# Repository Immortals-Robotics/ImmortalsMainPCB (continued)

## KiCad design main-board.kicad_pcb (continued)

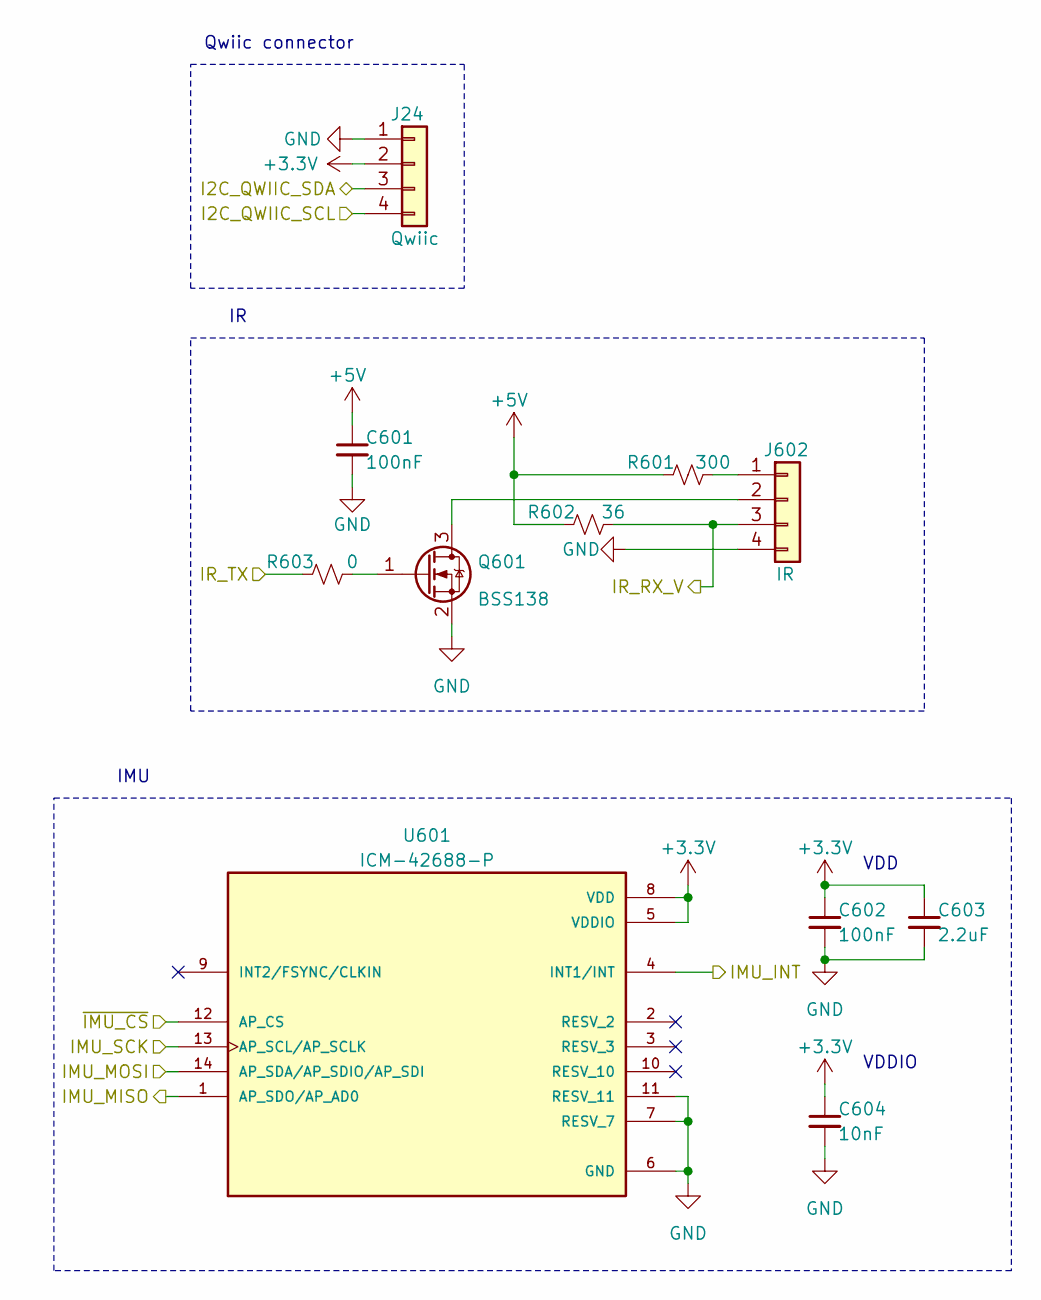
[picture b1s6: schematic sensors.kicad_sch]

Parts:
C601, C602: 100nF; C_0603_1608Metric; MPN RM EMK105 B7104KV-F
C603: 2.2uF; C_0805_2012Metric
C604: 10nF; C_0603_1608Metric
J24: Qwiic; JST_SH_SM04B-SRSS-TB_1x04-1MP_P1.00mm_Horizontal; MPN SM04B-SRSS-TB(LF)(SN)
J602: IR; JST_SH_SM04B-SRSS-TB_1x04-1MP_P1.00mm_Horizontal; MPN SM04B-SRSS-TB(LF)(SN)
Q601: BSS138; SOT-23
R601: 300; R_0603_1608Metric
R602: 36; R_0603_1608Metric
R603: 0; R_0603_1608Metric; MPN RMCF0603ZT0R00
U601: ICM-42688-P; PQFN50P300X250X97-14N

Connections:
+5V: C601.1, R601.1, R602.1; also elsewhere on the board
/CM_SPI1_MISO: U601.1 (AP_SDO/AP_AD0); also elsewhere on the board
/CM_SPI1_MOSI: U601.14 (AP_SDA/AP_SDIO/AP_SDI); also elsewhere on the board
/CM_SPI1_SCK: U601.13 (AP_SCL/AP_SCLK); also elsewhere on the board
/IMU_INT: U601.4 (INT1/INT); also elsewhere on the board
/IR_ADC: J602.3, R602.2; also elsewhere on the board
/IR_PWM: R603.1; also elsewhere on the board
/~CM_SPI1_CS_IMU: U601.12 (AP_CS); also elsewhere on the board
unnamed: J602.1, R601.2
unnamed: J602.2, Q601.3 (D)
unnamed: Q601.1 (G), R603.2

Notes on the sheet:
Qwiic connector
VDD
VDDIO
IMU

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
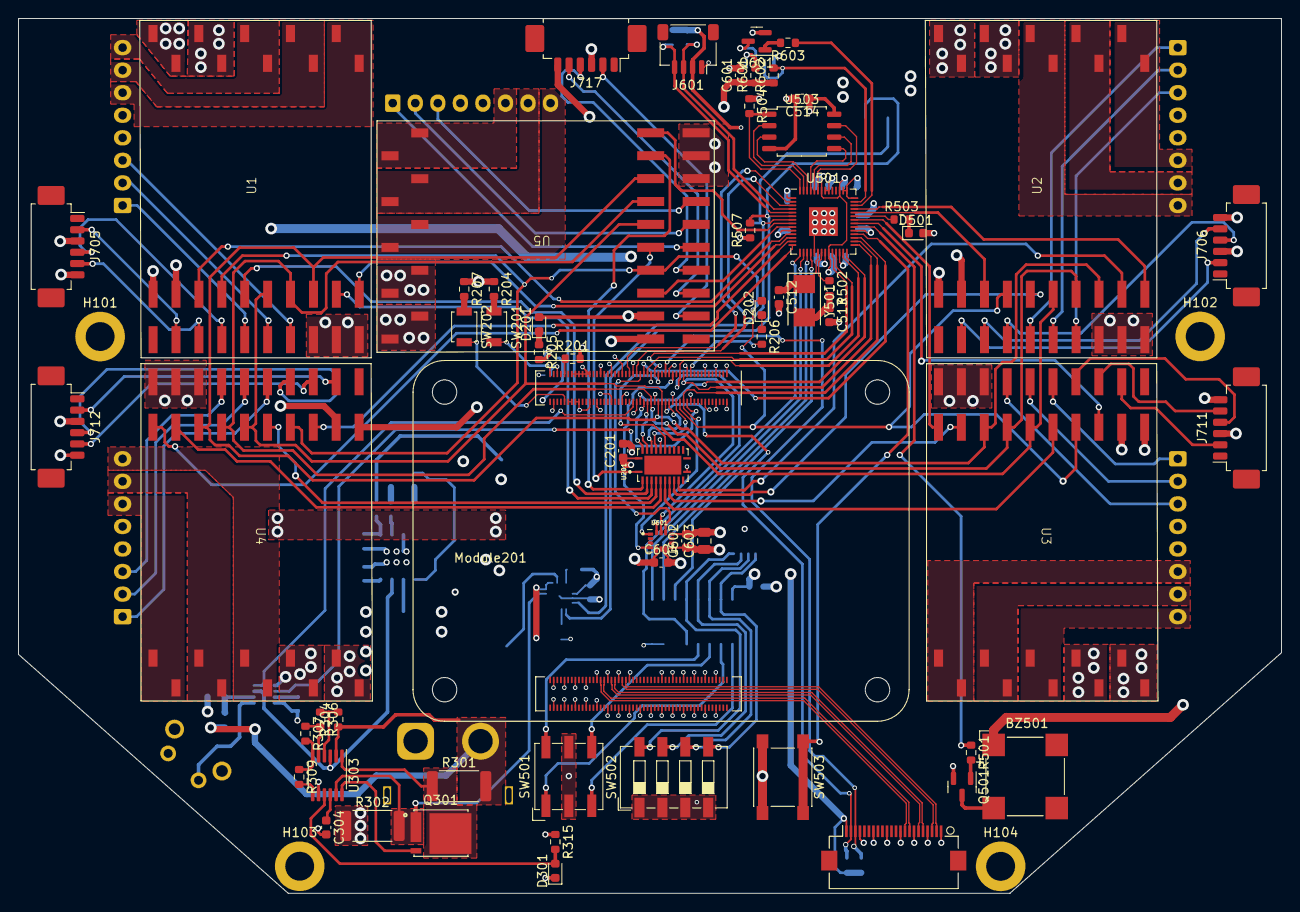
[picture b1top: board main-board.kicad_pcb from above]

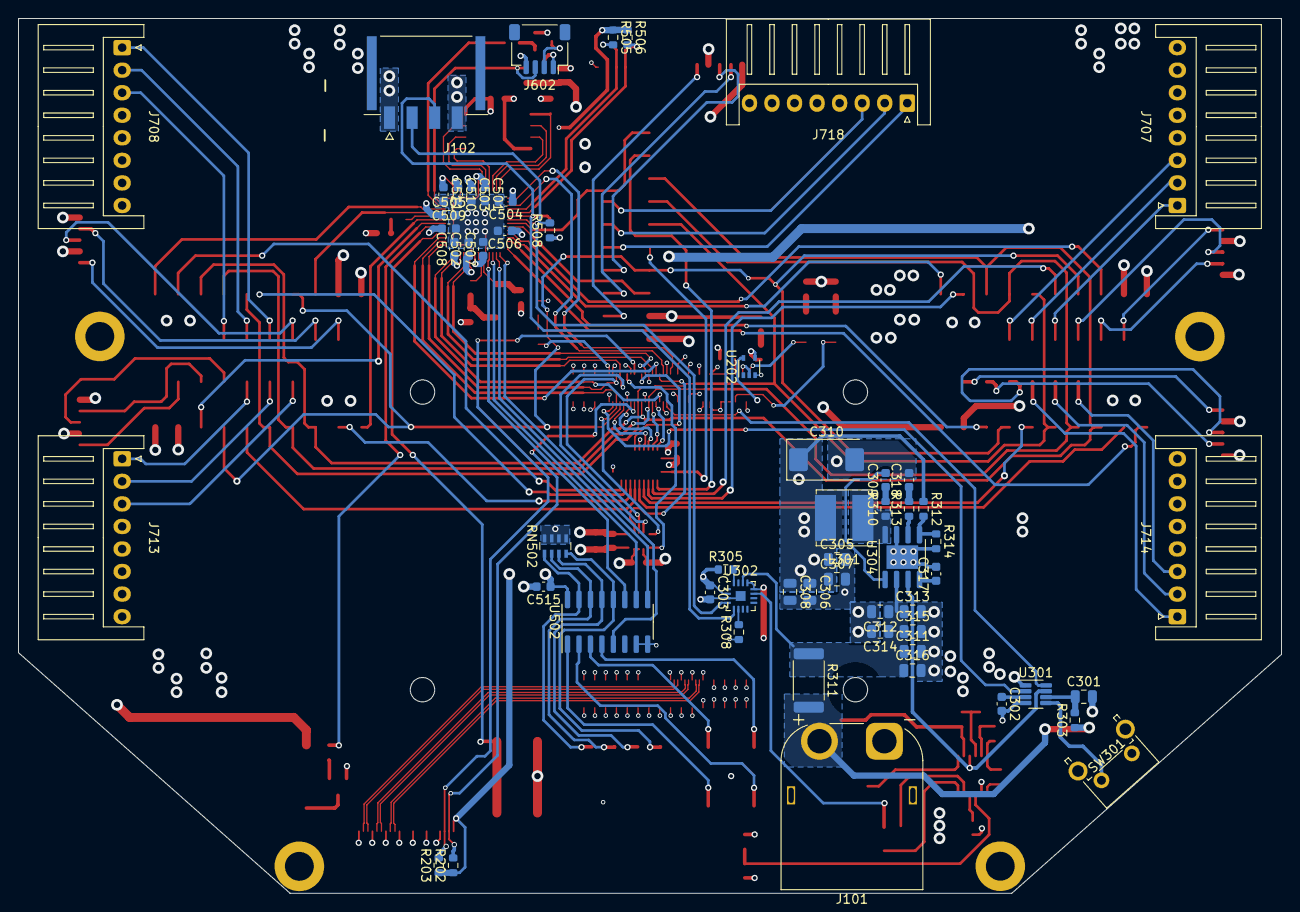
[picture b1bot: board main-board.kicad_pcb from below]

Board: 4 copper layers, 140.0 x 97.0 mm, 123 parts (58 on the bottom side), 171 nets.

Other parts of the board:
D301, D501: LED Green; LED_0603_1608Metric
J101: Battery; AMASS_XT60PW-M_1x02_P7.20mm_Horizontal
J601: Qwiic; JST_SH_SM04B-SRSS-TB_1x04-1MP_P1.00mm_Horizontal
Q501: BSS138; SOT-23
R315, R503: 1K; R_0603_1608Metric
R501: 0; R_0603_1608Metric

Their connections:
+BATT: J101.2; also elsewhere on the board
/MICRO_I2C1_SCL: J601.4; also elsewhere on the board
/MICRO_I2C1_SDA: J601.3; also elsewhere on the board
/Micro/BUZZER: R501.1; also elsewhere on the board
unnamed 136: Q501.3 (D); also elsewhere on the board
unnamed: D501.1 (K), R503.2
unnamed: Q501.1 (G), R501.2
unnamed 167: R503.1; also elsewhere on the board

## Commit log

2016-05-02 Initial submission, finally found it :D
2016-06-01 Added pcb images
2016-06-01 Added readme file
2016-06-01 Added 2d image
2016-06-01 Updated readme file
2023-05-06 Rev 2.0 of the main pcb, designed by Omid and Mrnik in 2018.
2023-05-07 Remove the old altium files and create the new kicad project.
2023-05-10 Doing schematics, almost done.
2023-05-10 Allocate GPIOs.
2023-05-10 Finish motor schematics.
2023-05-10 Move sensors to one sheet.
2023-05-10 Unify CM4 sub-sheets.
2023-05-10 Add RP2040
2023-05-14 Finish RP2040 connections.
2023-05-15 Finish connecting everything in sch.
2023-05-15 Fix sch errors and warnings.
2023-05-15 Assign some of the footprints and MPNs.
2023-05-17 Import the previous main board to match the overall shape, and re-annotate the schematic.
2023-05-17 Start placing parts on pcb.
2023-05-18 Place all the components on the PCB.
2023-05-21 Finish the draft routing.
2023-05-21 Fix motor winding order.
2023-05-21 Improve routings,
2023-05-22 Improve routings.
2023-05-22 Fixed silkscreen and added teardrops.
2023-05-22 Add version text.
2023-05-22 Update MPNs.
2023-05-29 Add MPNs for CM4 and motor drivers.
2023-05-29 Update MPNs in the PCB as well.
2023-06-02 Add missing 3d models.
2023-06-05 Fix the issues found during testing in schematics.
2023-06-05 Applied the fixes to the PCB as well.
2023-06-05 More refinements to the PCB.
2023-06-09 Use parts similar to other boards where possible.
2023-06-09 Change on-board LEDs to vertical diffuse.
2023-06-11 Fix the 24v sense res and the IR port MPN.
2023-06-11 Add the ibom config file.
